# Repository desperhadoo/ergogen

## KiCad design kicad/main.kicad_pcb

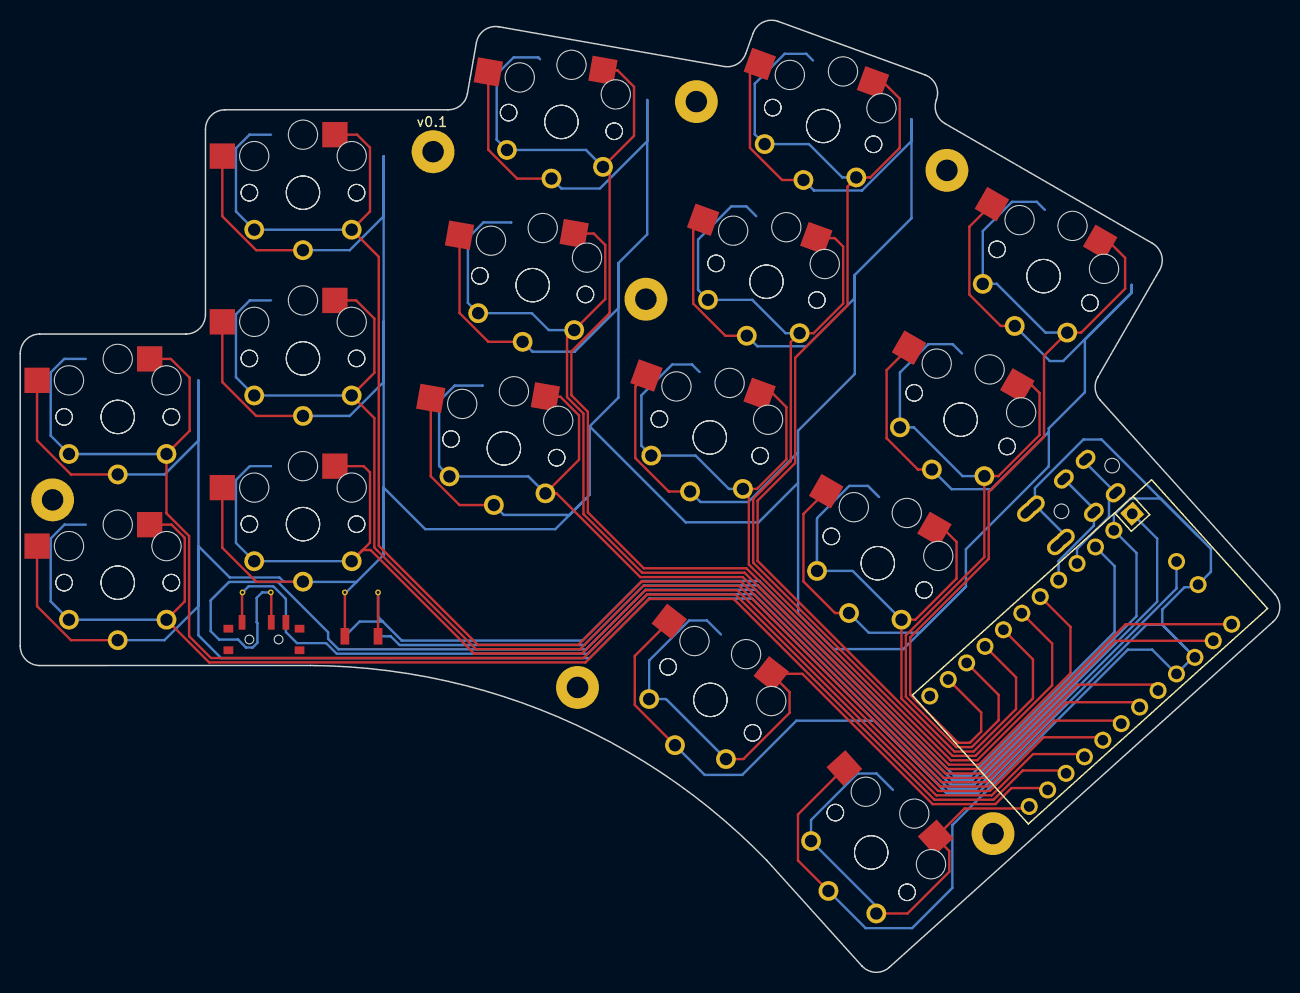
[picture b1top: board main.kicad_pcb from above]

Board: 2 copper layers, 129.2 x 97.7 mm, 33 parts (0 on the bottom side), 17 nets.

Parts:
MCU1: ProMicro
S1, S2, S3, S4, S5, S6, S7, S8, S9, S10, S11, S12, S13, S14, S15, S16, S17, S18, S19, S20, S21, S22, S23, S24, S25, S26, S27, S28, S29, S30, S31, S32: PG1350

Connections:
GND: MCU1.2, MCU1.15, MCU1.16, S1.2, S2.2, S3.2, S4.2, S5.2, S6.2, S7.2, S8.2, S9.2, S10.2, S11.2, S12.2, S13.2, S14.2, S15.2, S16.2, S17.2, S18.2, S19.2, S20.2, S21.2, S22.2, S23.2, S24.2, S25.2, S26.2, S27.2, S28.2, S29.2, S30.2, S31.2, S32.2
P0: MCU1.14, S13.1, S14.1
P1: MCU1.13, S15.1, S16.1
P2: MCU1.17, S11.1, S12.1
P3: MCU1.18, S9.1, S10.1
P4: MCU1.19, S7.1, S8.1
P5: MCU1.20, S5.1, S6.1
P6: MCU1.21, S3.1, S4.1
P7: MCU1.22, S1.1, S2.1
P8: MCU1.23, S29.1, S30.1
P9: MCU1.24, S31.1, S32.1
P14: MCU1.10, S25.1, S26.1
P15: MCU1.9, S23.1, S24.1
P16: MCU1.11, S27.1, S28.1
P18: MCU1.8, S21.1, S22.1
P19: MCU1.7, S19.1, S20.1
P20: MCU1.6, S17.1, S18.1

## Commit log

2022-05-07 Created first layout
2022-05-07 Added kicad project
